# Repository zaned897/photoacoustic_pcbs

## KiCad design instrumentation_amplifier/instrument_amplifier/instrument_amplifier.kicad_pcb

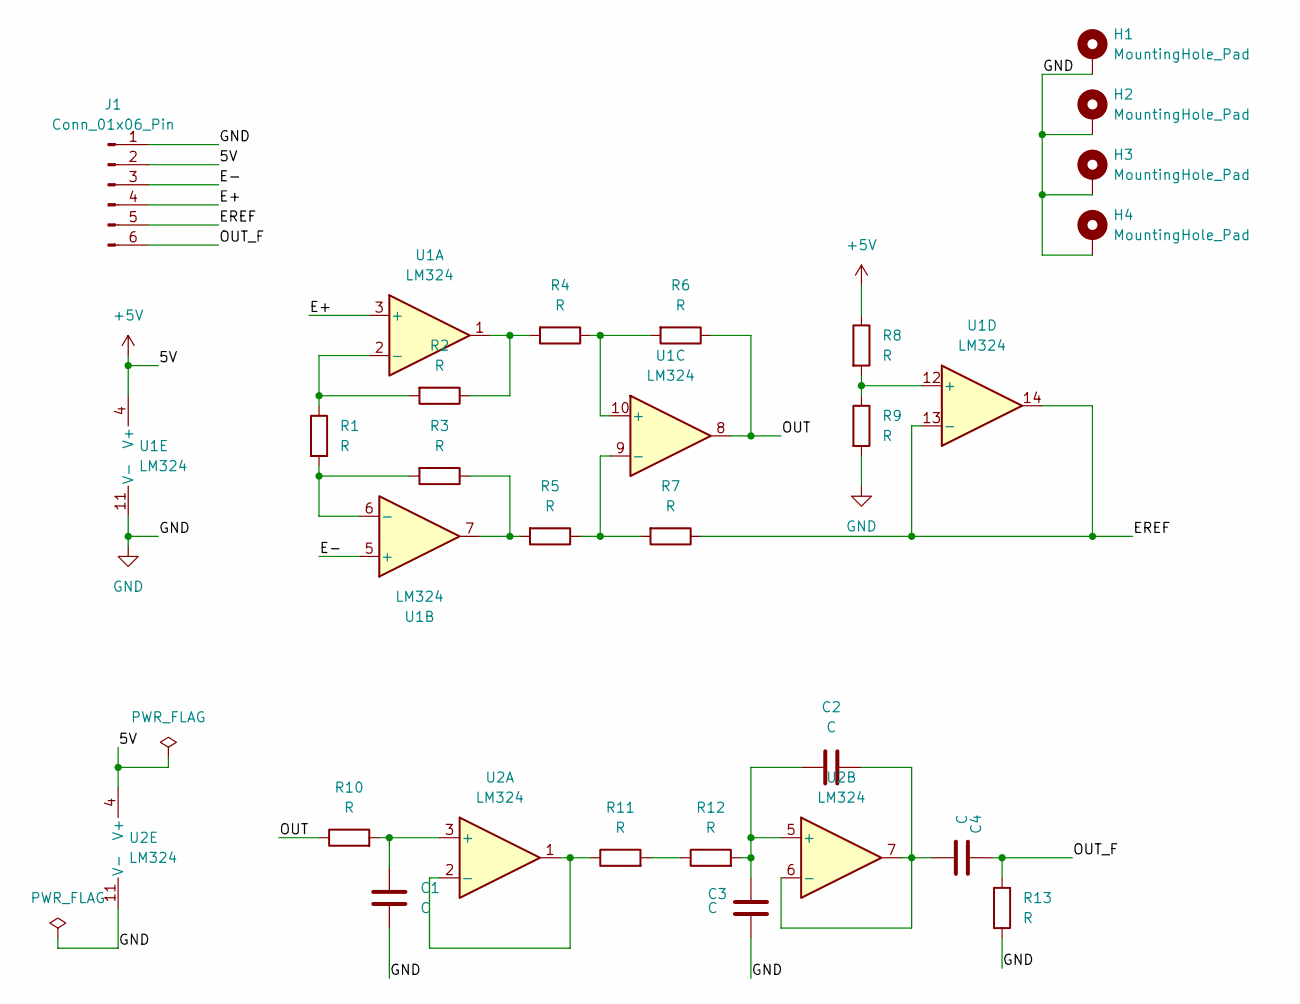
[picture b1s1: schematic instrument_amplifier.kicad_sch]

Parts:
C1, C2, C3, C4: C; C_Radial_D8.0mm_H11.5mm_P3.50mm
H1, H2, H3, H4: MountingHole_Pad; MountingHole_2.5mm_Pad
J1: Conn_01x06_Pin; PinHeader_1x06_P2.54mm_Horizontal
R1, R2, R3, R4, R5, R6, R7, R8, R9, R10, R11, R12, R13: R; R_Axial_DIN0207_L6.3mm_D2.5mm_P7.62mm_Horizontal
U1, U2: LM324; DIP-14_W7.62mm

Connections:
+5V: J1.2, R8.1, U1.4 (V+), U2.4 (V+)
/E+: J1.4, U1.3 (+)
/E-: J1.3, U1.5 (+)
/EREF: J1.5, R7.1, U1.13 (-), U1.14
/OUT: R6.1, R10.1, U1.8
/OUT_F: C4.1, J1.6, R13.2
GND: C1.2, C3.2, H1.1, H2.1, H3.1, H4.1, J1.1, R9.2, R13.1, U1.11 (V-), U2.11 (V-)
unnamed: R2.1, R4.2, U1.1
unnamed: R3.1, R5.2, U1.7
unnamed: R11.2, R12.1
unnamed: R1.1, R2.2, U1.2 (-)
unnamed: R1.2, R3.2, U1.6 (-)
unnamed: R4.1, R6.2, U1.10 (+)
unnamed: R5.1, R7.2, U1.9 (-)
unnamed: R8.2, R9.1, U1.12 (+)
unnamed: C1.1, R10.2, U2.3 (+)
unnamed: R11.1, U2.1, U2.2 (-)
unnamed: C2.1, C3.1, R12.2, U2.5 (+)
unnamed: C2.2, C4.2, U2.6 (-), U2.7

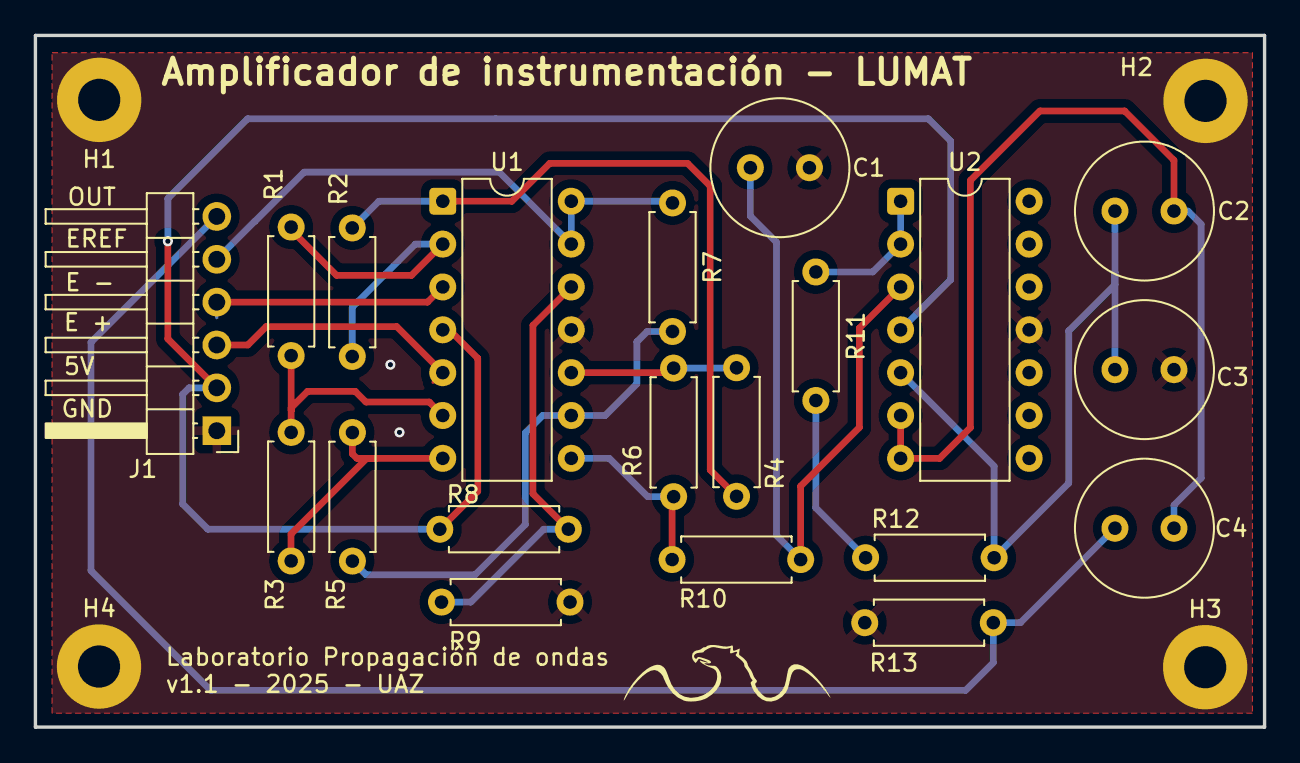
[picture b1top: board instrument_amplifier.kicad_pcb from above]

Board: 2 copper layers, 72.9 x 41.0 mm, 24 parts (0 on the bottom side), 19 nets.

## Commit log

2025-11-07 init commit
2025-11-07 feat: opamp first version ready to review
2025-11-15 final commit, ready to fab
